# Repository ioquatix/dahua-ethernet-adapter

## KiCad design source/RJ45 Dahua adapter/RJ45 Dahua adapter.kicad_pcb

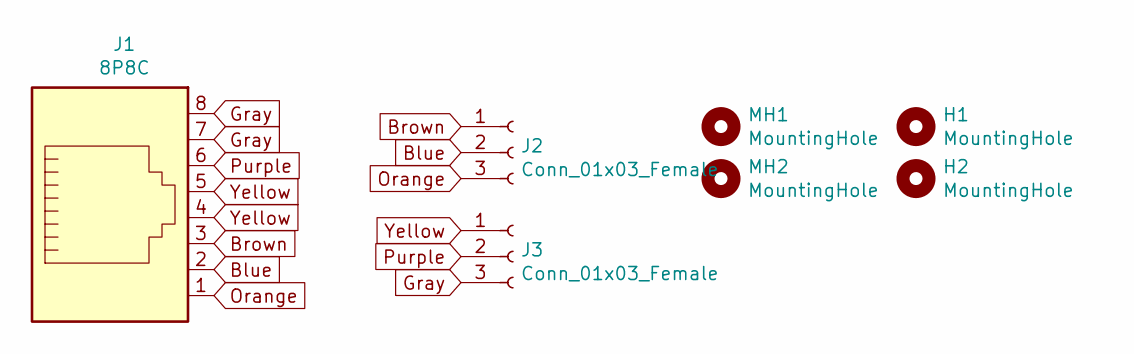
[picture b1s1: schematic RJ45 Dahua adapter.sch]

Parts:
H1, H2: MountingHole
J1: 8P8C; RJ45_Amphenol_54602-x08_Horizontal
J2, J3: Conn_01x03_Female; PinHeader_1x03_P2.54mm_Vertical
MH1, MH2: MountingHole; MountingHole_3mm

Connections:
Blue: J1.2, J2.2
Brown: J1.3, J2.1
Gray: J1.7, J1.8, J3.3
Orange: J1.1, J2.3
Purple: J1.6, J3.2
Yellow: J1.4, J1.5, J3.1

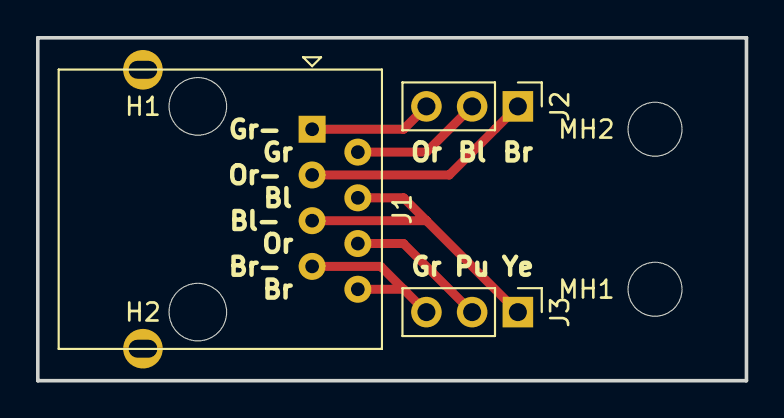
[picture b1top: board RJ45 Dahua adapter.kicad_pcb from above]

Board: 2 copper layers, 39.4 x 19.1 mm, 7 parts (0 on the bottom side), 6 nets.

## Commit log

2018-11-07 Initial PCB design based on pinout.
